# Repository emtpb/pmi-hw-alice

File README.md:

# PMI Advanced Lights I2C Extension (ALICE)

This pcb is designed for the course PMI (Practical course Microcontroller
and Interface electronics) to model crossroads with traffic lights. It uses
an I2C port expander to drive several leds.

Pin header and sockets are compatible with
[Digilents Pmod](https://digilent.com/reference/pmod/start) interface.

The board can be used with [PMI's BoB²](https://github.com/emtpb/pmi-hw-bob2)
pcb.

# Interactive BOM

An interactive html BOM page with pcb layout and material placement can be found [here](https://emtpb.github.io/pmi-hw-alice/bom/ibom.html).

# Changelog

## 1.0
* First prototype

## 1.1
* First release

## 1.2
* Add reset bridge to be able to reset the ic at power up

## 1.3
* Convert project to Kicad 6
* Round pcb corners

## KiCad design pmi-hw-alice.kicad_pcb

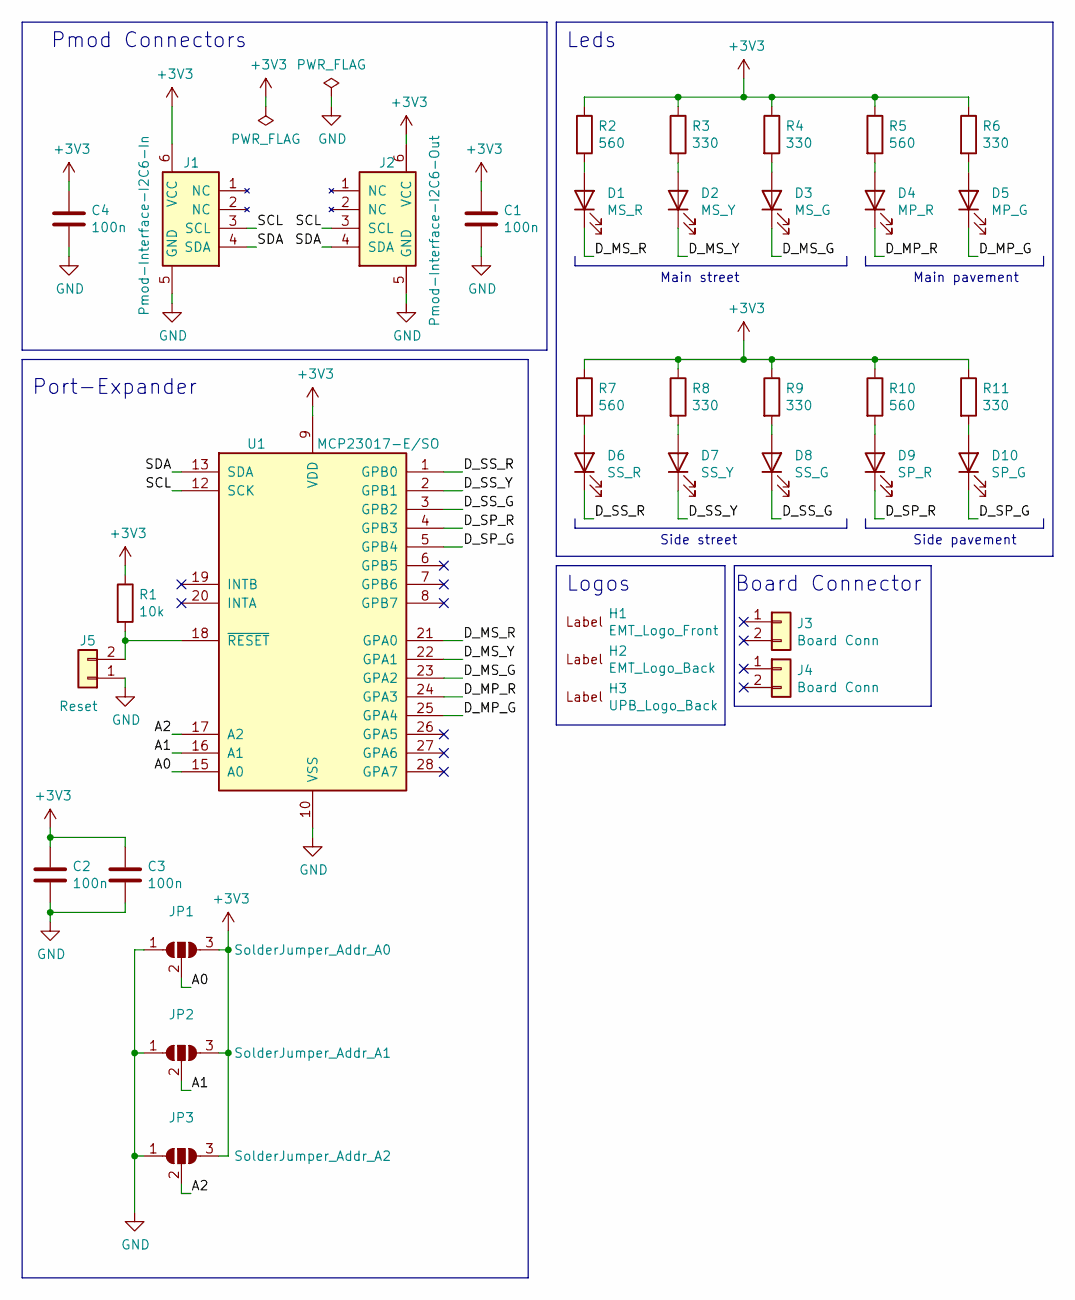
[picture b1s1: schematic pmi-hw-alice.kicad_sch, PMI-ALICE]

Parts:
C1, C2, C3, C4: 100n; C_0603_1608Metric
D1: MS_R; LED_0603_1608Metric; Manufacturer Part No LS L29K-G1H2-1-Z; Mouser Part No 720-LSL29K-G1H2-1-Z
D2: MS_Y; LED_0603_1608Metric; Manufacturer Part No LY L29K-H1K2-26; Mouser Part No 720-LYL29KH1K226Z
D3: MS_G; LED_0603_1608Metric; Manufacturer Part No LG L29K-F2J1-24-Z; Mouser Part No 720-LGL29KF2J124Z
D4: MP_R; LED_0603_1608Metric; Manufacturer Part No LS L29K-G1H2-1-Z; Mouser Part No 720-LSL29K-G1H2-1-Z
D5: MP_G; LED_0603_1608Metric; Manufacturer Part No LG L29K-F2J1-24-Z; Mouser Part No 720-LGL29KF2J124Z
D6: SS_R; LED_0603_1608Metric; Manufacturer Part No LS L29K-G1H2-1-Z; Mouser Part No 720-LSL29K-G1H2-1-Z
D7: SS_Y; LED_0603_1608Metric; Manufacturer Part No LY L29K-H1K2-26; Mouser Part No 720-LYL29KH1K226Z
D8: SS_G; LED_0603_1608Metric; Manufacturer Part No LG L29K-F2J1-24-Z; Mouser Part No 720-LGL29KF2J124Z
D9: SP_R; LED_0603_1608Metric; Manufacturer Part No LS L29K-G1H2-1-Z; Mouser Part No 720-LSL29K-G1H2-1-Z
D10: SP_G; LED_0603_1608Metric; Manufacturer Part No LG L29K-F2J1-24-Z; Mouser Part No 720-LGL29KF2J124Z
H1: EMT_Logo_Front; EMT-Logo_5.1x2.5mm_Silkscreen
H2: EMT_Logo_Back; EMT-Logo_8.2x4.1mm_Silkscreen
H3: UPB_Logo_Back; UPB-Logo_En_12.3X4.3mm
J1: Pmod-Interface-I2C6-In; Pmod_Interface_Male6
J2: Pmod-Interface-I2C6-Out; Pmod_Interface_Female6
J3: Board Conn; PinHeader_1x02_P2.54mm_Horizontal
J4: Board Conn; PinSocket_1x02_P2.54mm_Horizontal
J5: Reset; PinHeader_1x02_P1.27mm_Vertical
JP1: SolderJumper_Addr_A0; SolderJumper-3_P2.0mm_Open_TrianglePad1.0x1.5mm
JP2: SolderJumper_Addr_A1; SolderJumper-3_P2.0mm_Open_TrianglePad1.0x1.5mm
JP3: SolderJumper_Addr_A2; SolderJumper-3_P2.0mm_Open_TrianglePad1.0x1.5mm
R1: 10k; R_0603_1608Metric
R2, R5, R7, R10: 560; R_0603_1608Metric
R3, R4, R6, R8, R9, R11: 330; R_0603_1608Metric
U1: MCP23017-E/SO; SOIC-28W_7.5x17.9mm_P1.27mm; Mouser Part No 579-MCP23017-E/SO

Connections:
+3V3: C1.1, C2.1, C3.1, C4.1, J1.6 (VCC), J2.6 (VCC), JP1.3 (B), JP2.3 (B), JP3.3 (B), R1.1, R2.1, R3.1, R4.1, R5.1, R6.1, R7.1, R8.1, R9.1, R10.1, R11.1, U1.9 (VDD)
/A0: JP1.2 (C), U1.15 (A0)
/A1: JP2.2 (C), U1.16 (A1)
/A2: JP3.2 (C), U1.17 (A2)
/D_MP_G: D5.1 (K), U1.25 (GPA4)
/D_MP_R: D4.1 (K), U1.24 (GPA3)
/D_MS_G: D3.1 (K), U1.23 (GPA2)
/D_MS_R: D1.1 (K), U1.21 (GPA0)
/D_MS_Y: D2.1 (K), U1.22 (GPA1)
/D_SP_G: D10.1 (K), U1.5 (GPB4)
/D_SP_R: D9.1 (K), U1.4 (GPB3)
/D_SS_G: D8.1 (K), U1.3 (GPB2)
/D_SS_R: D6.1 (K), U1.1 (GPB0)
/D_SS_Y: D7.1 (K), U1.2 (GPB1)
/SCL: J1.3 (SCL), J2.3 (SCL), U1.12 (SCK)
/SDA: J1.4 (SDA), J2.4 (SDA), U1.13 (SDA)
GND: C1.2, C2.2, C3.2, C4.2, J1.5 (GND), J2.5 (GND), J5.1, JP1.1 (A), JP2.1 (A), JP3.1 (A), U1.10 (VSS)
unnamed: D1.2 (A), R2.2
unnamed: D2.2 (A), R3.2
unnamed: D3.2 (A), R4.2
unnamed: D4.2 (A), R5.2
unnamed: D5.2 (A), R6.2
unnamed: D6.2 (A), R7.2
unnamed: D7.2 (A), R8.2
unnamed: D8.2 (A), R9.2
unnamed: D9.2 (A), R10.2
unnamed: D10.2 (A), R11.2
unnamed: J5.2, R1.2, U1.18 (~RESET)

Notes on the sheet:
Main pavement
Main street
Side pavement
Leds
Side street
Pmod Connectors
Port-Expander
Board Connector
Logos

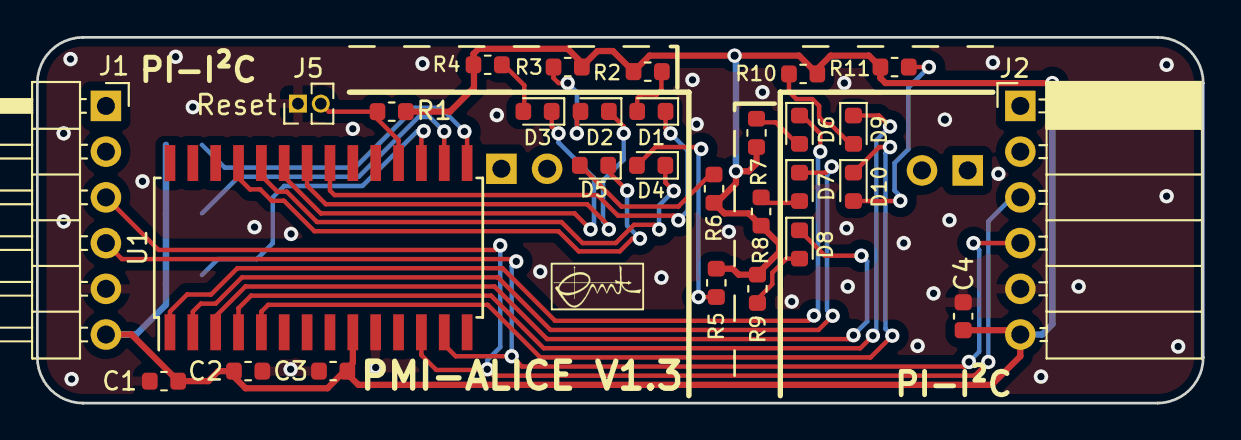
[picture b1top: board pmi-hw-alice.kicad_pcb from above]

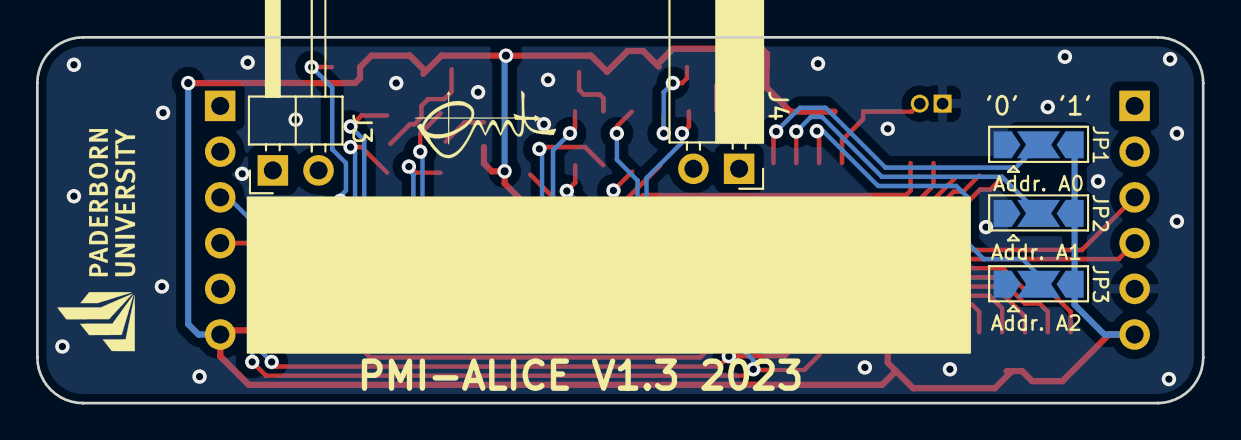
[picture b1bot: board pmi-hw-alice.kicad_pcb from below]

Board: 2 copper layers, 64.8 x 20.3 mm, 37 parts (7 on the bottom side), 28 nets.

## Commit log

2021-12-21 Initial revision
2021-12-23 Bump to V1.2
    * Add reset bridge to be able to reset the ic at power up
2023-02-21 Bump to V1.3
2025-05-22 Add interactive BOM link
